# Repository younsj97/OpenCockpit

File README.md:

# OpenCockpit

OpenCockpit is an open-source FPV cockpit display that uses a Raspberry Pi.  
It consists of working displays such as a HUD,MAP,MFD,INFO and it receives data from the flight controller(FC) to show live flight data in real time.

---

## Full Build Tutuorial
  - [English](https://vudev.notion.site/OpenCockpit-Build-Tutorial-3566ea6262ea80a49489f02d480d7f26?source=copy_link)
  - [한국어](https://vudev.notion.site/OpenCockpit-3566ea6262ea80b49948cab48c1eeefa?source=copy_link)

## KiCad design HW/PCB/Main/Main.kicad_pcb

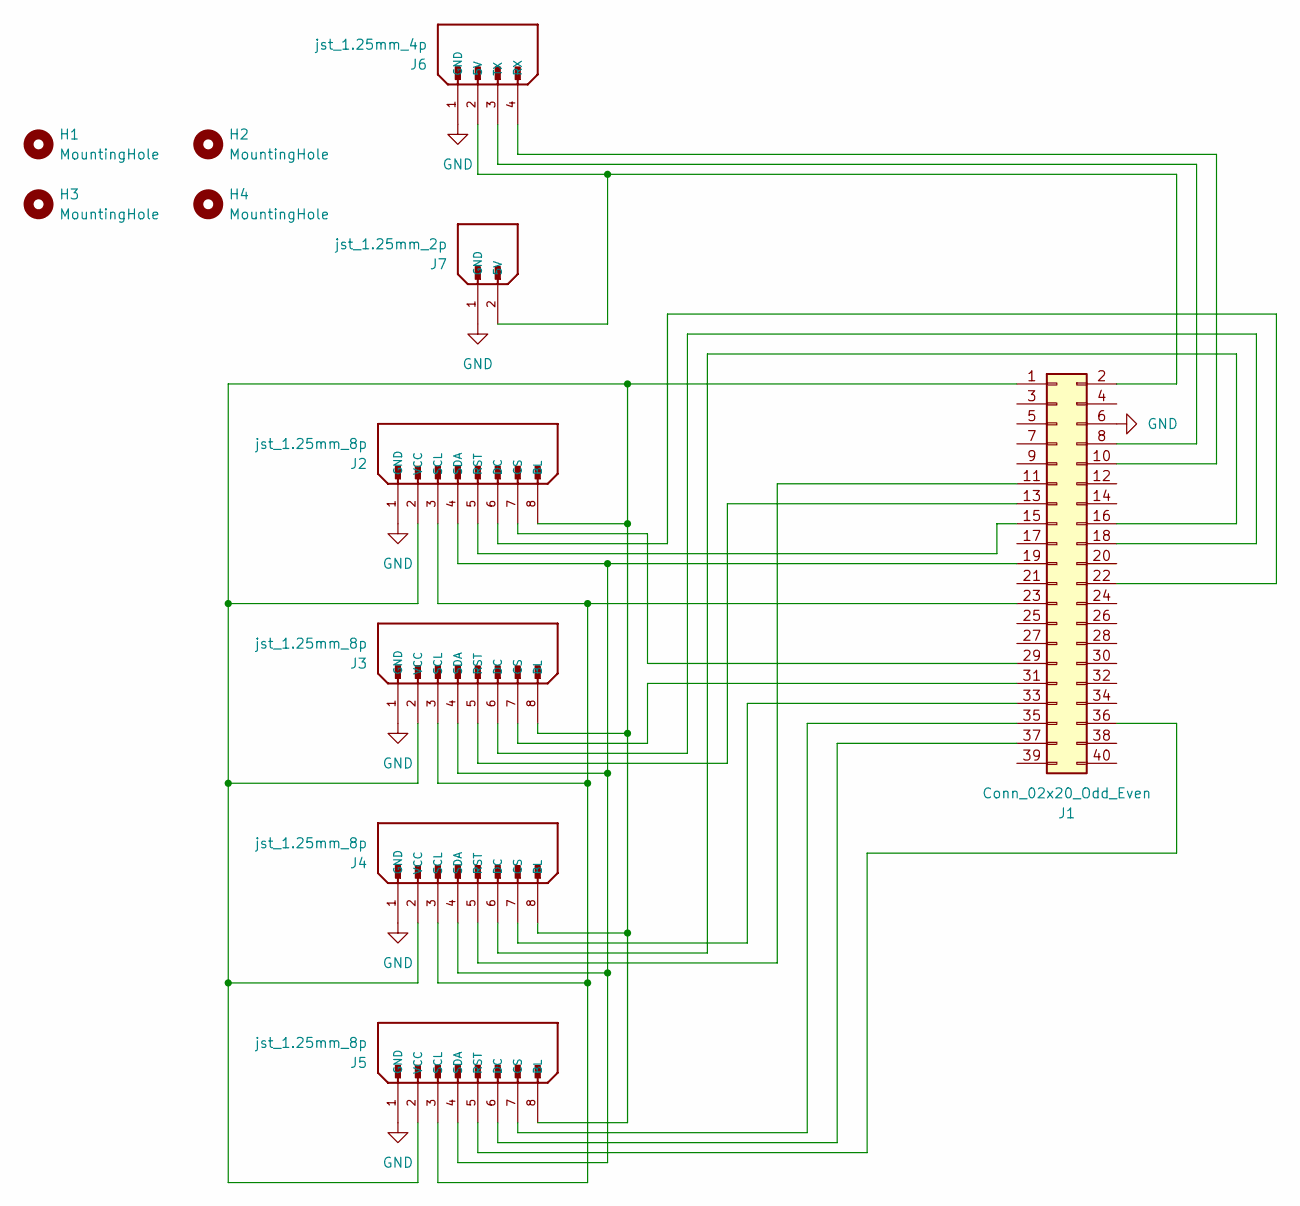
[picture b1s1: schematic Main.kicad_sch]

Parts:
H1, H2, H3, H4: MountingHole; MountingHole_2.2mm_M2
J1: Conn_02x20_Odd_Even; PinSocket_2x20_P2.54mm_Vertical
J2, J3, J4, J5: jst_1.25mm_8p
J6: jst_1.25mm_4p
J7: jst_1.25mm_2p

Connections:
GND: J1.6 (GND), J2.1 (GND), J3.1 (GND), J4.1 (GND), J5.1 (GND), J6.1 (GND), J7.1 (GND)
unnamed: J1.1 (3.3V), J2.2 (VCC), J2.8 (BL), J3.2 (VCC), J3.8 (BL), J4.2 (VCC), J4.8 (BL), J5.2 (VCC), J5.8 (BL)
unnamed: J1.29 (DP1_CS), J2.7 (CS)
unnamed: J1.22 (DP1_DC), J2.6 (DC)
unnamed: J1.15 (DP1_RST), J2.5 (RST)
unnamed: J1.31 (DP2_CS), J3.7 (CS)
unnamed: J1.18 (DP2_DC), J3.6 (DC)
unnamed: J1.13 (DP2_RST), J3.5 (RST)
unnamed: J1.33 (DP3_CS), J4.7 (CS)
unnamed: J1.16 (DP3_DC), J4.6 (DC)
unnamed: J1.11 (DP3_RST), J4.5 (RST)
unnamed: J1.35 (DP4_CS), J5.7 (CS)
unnamed: J1.37 (DP4_DC), J5.6 (DC)
unnamed: J1.36 (DP4_RST), J5.5 (RST)
unnamed: J1.8, J6.3 (TX)
unnamed: J1.10, J6.4 (RX)
unnamed: J1.23 (SCK), J2.3 (SCL), J3.3 (SCL), J4.3 (SCL), J5.3 (SCL)
unnamed: J1.19 (SDA), J2.4 (SDA), J3.4 (SDA), J4.4 (SDA), J5.4 (SDA)
unnamed: J1.2 (5V), J6.2 (5V), J7.2 (5V)

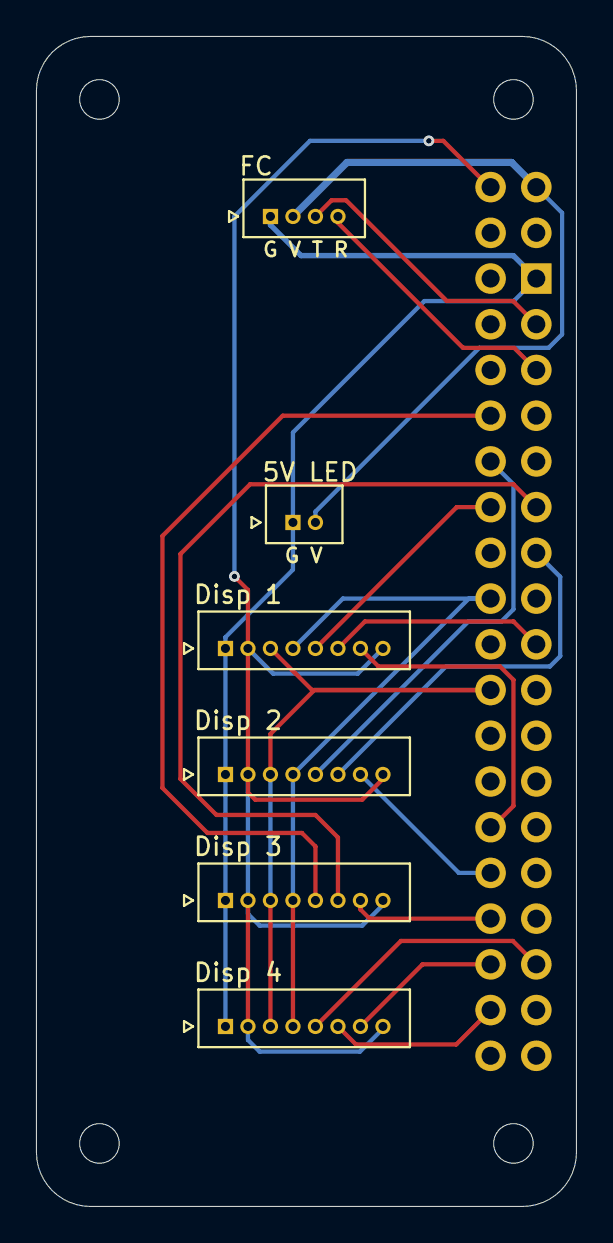
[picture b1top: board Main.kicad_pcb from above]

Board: 2 copper layers, 30.0 x 65.0 mm, 11 parts (0 on the bottom side), 19 nets.
